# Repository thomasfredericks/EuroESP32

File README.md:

# EuroESP32
 Eurorack version of the ESP32 made to develop modules.

## Features
* 2x audio in 24bits
* 2x audio out 24bits
* 4x CV in (-5V to 5V) 12bits
* 4x CV out (0V to 5V) 12bits

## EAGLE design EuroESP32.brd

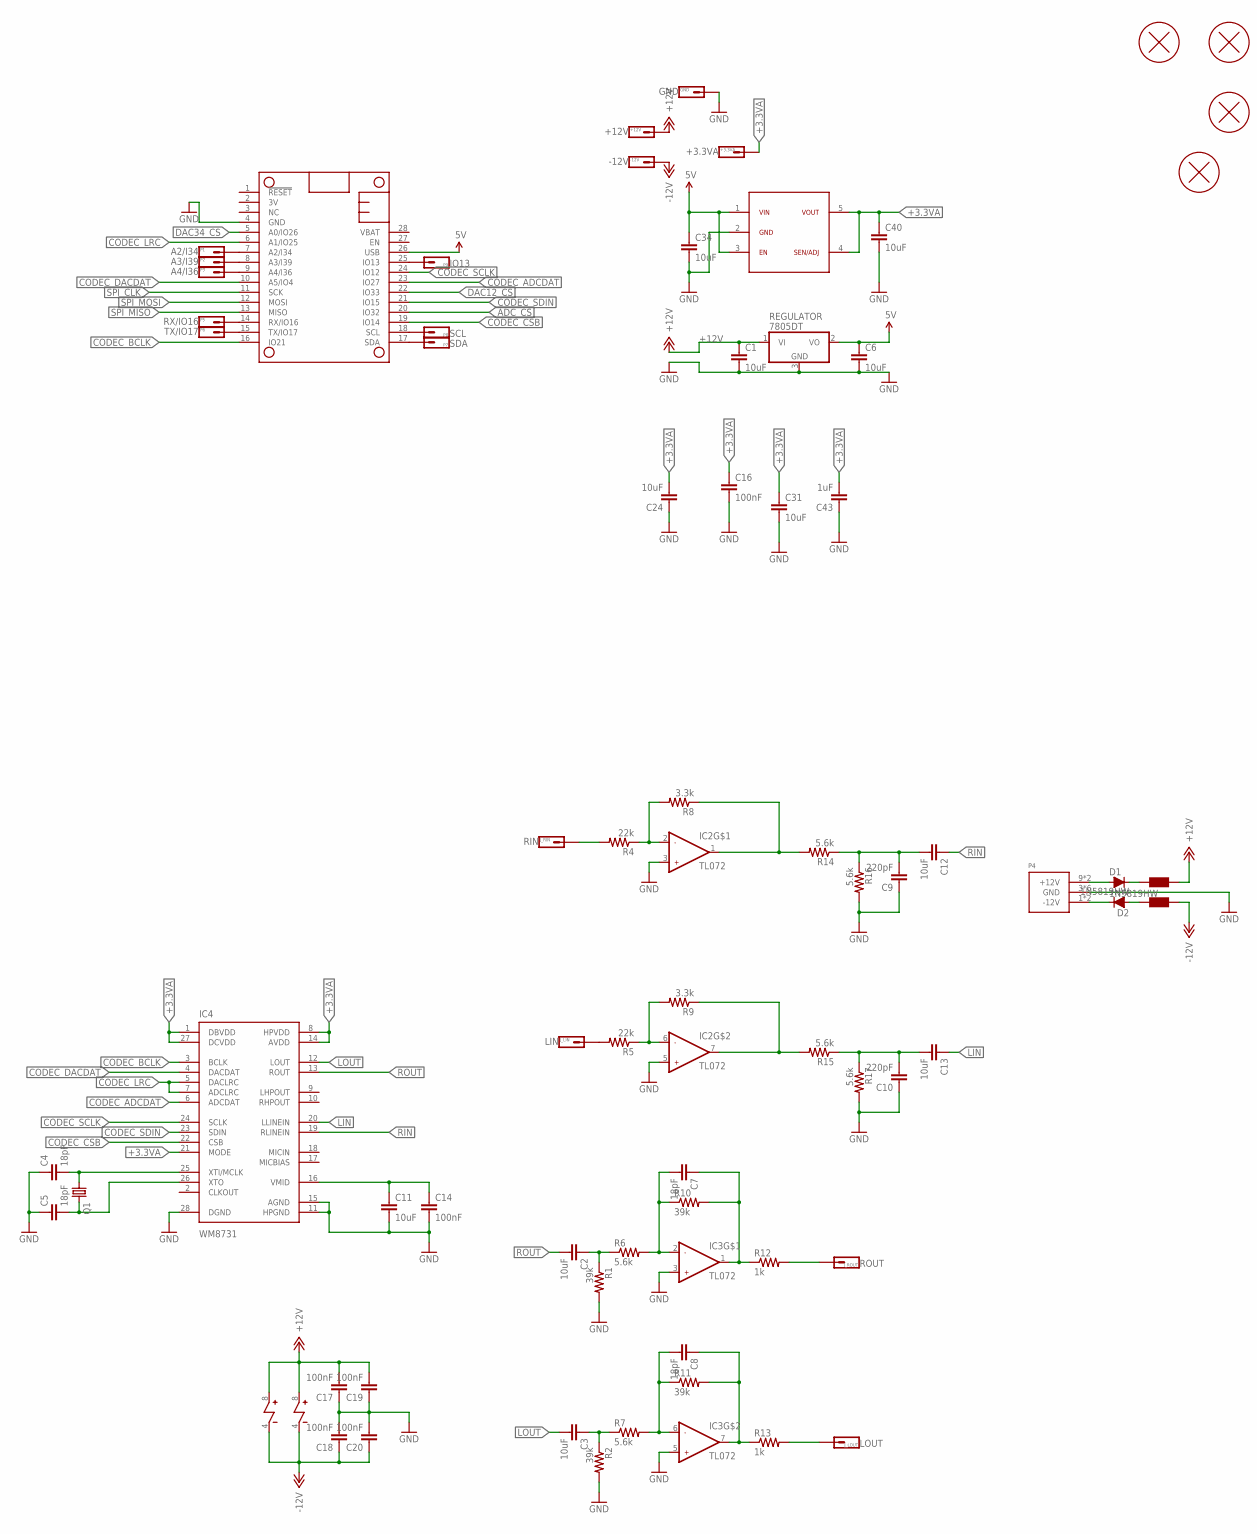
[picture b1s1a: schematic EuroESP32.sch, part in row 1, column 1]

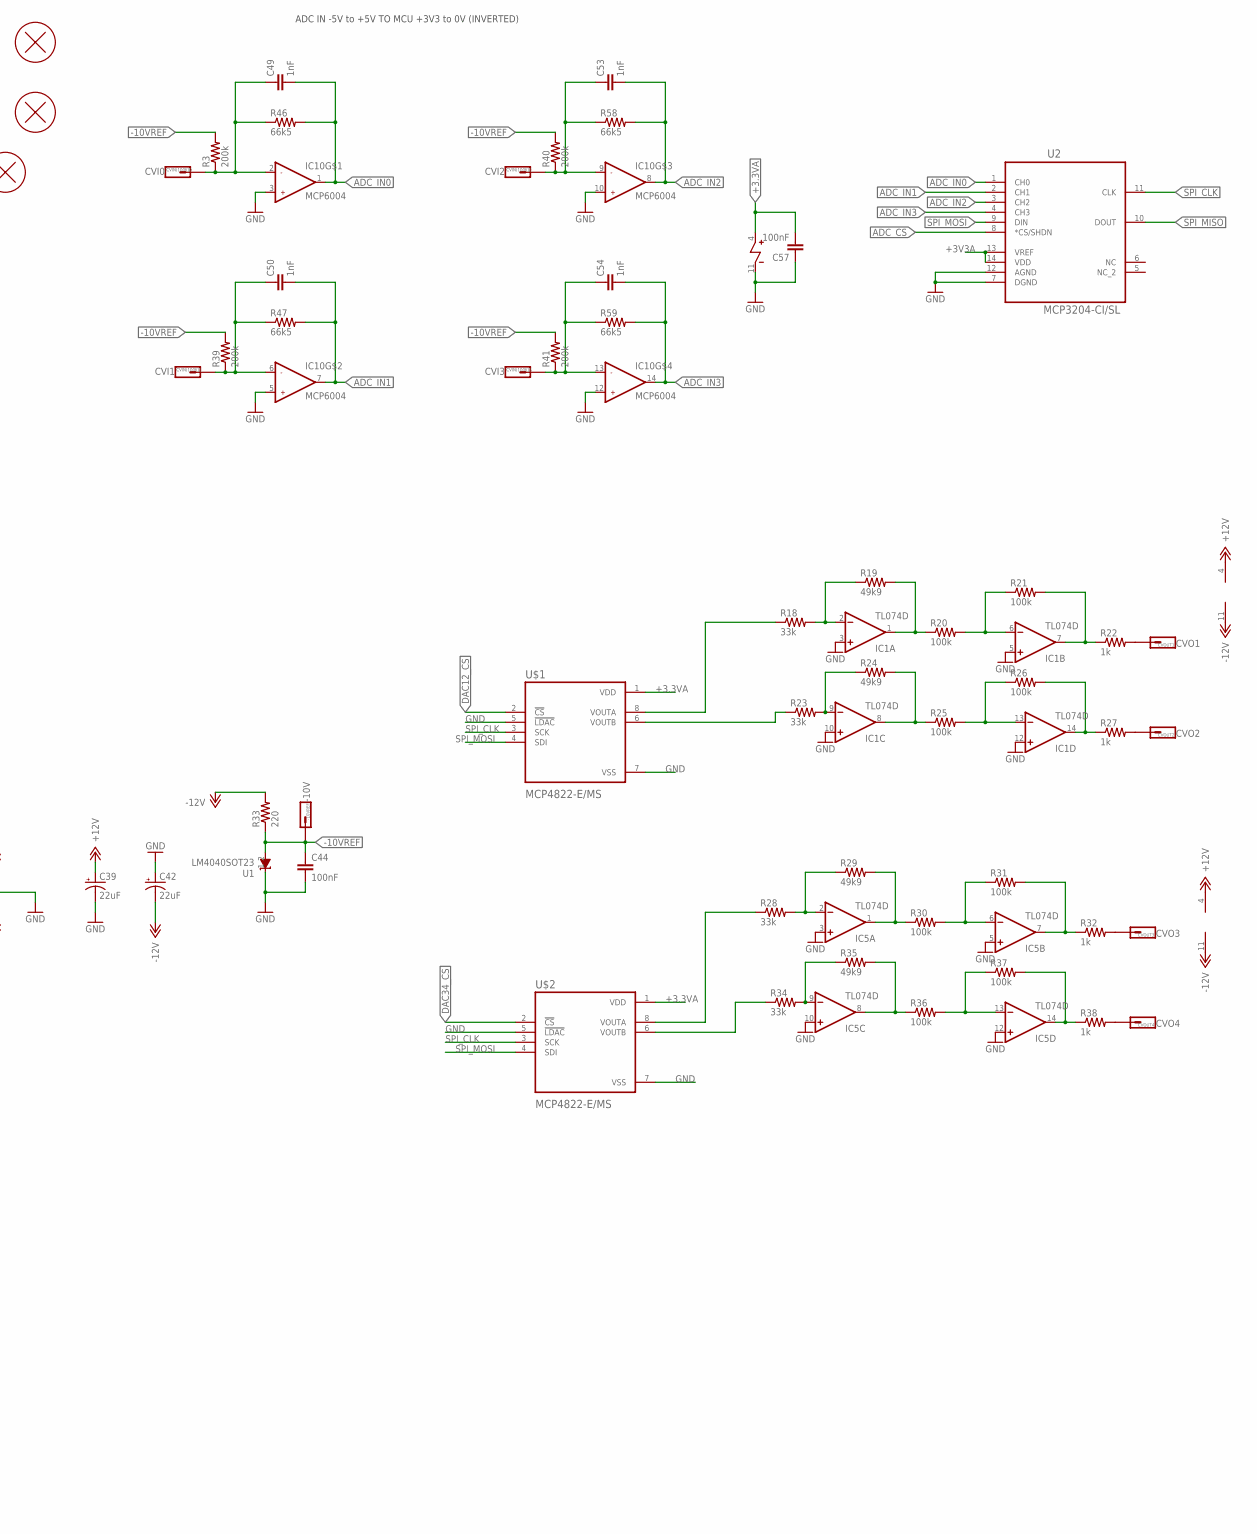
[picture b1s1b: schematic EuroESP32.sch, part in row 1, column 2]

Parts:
+3.3VA: +3.3VA; 1X01_SIDE_NAME
+12V: +12V; 1X01_SIDE_NAME
-10VREF: -10V; 1X01_SIDE_NAME
-12V: -12V; 1X01_SIDE_NAME
C1, C6, C34: 10uF; R1210
C2, C3, C11, C12, C13, C24, C31, C40: 10uF; R0805
C4, C5, C7, C8: 18pF; RESISTOR_0603
C9, C10: 220pF; RESISTOR_0603
C14, C16, C17, C18, C19, C20, C44, C57: 100nF; RESISTOR_0603
C39, C42: 22uF; 1206_POL
C43: 1uF; RESISTOR_0603
C49, C50, C53, C54: 1nF; RESISTOR_0603
CVIN(100K)0: CVI0; 1X01_SIDE_NAME
CVIN(100K)1: CVI1; 1X01_SIDE_NAME
CVIN(100K)2: CVI2; 1X01_SIDE_NAME
CVIN(100K)3: CVI3; 1X01_SIDE_NAME
CVOUT1: CVO1; 1X01_SIDE_NAME
CVOUT2: CVO2; 1X01_SIDE_NAME
CVOUT3: CVO3; 1X01_SIDE_NAME
CVOUT4: CVO4; 1X01_SIDE_NAME
D1, D2: 1N5819HW; SOD123
F1, F2: Würth Electronics 742792664; R0805
GND: GND; 1X01_SIDE_NAME
H1, H3, H4, H5: PCB_SCREW
IC1, IC5: TL074D; SO14
IC2, IC3: TL072; SOIC8
IC4: WM8731; SSOP28
IC7: ADP7118; SOT23-5L
IC10: MCP6004; TSSOP14
J_LIN: LIN; 1X01_SIDE_NAME
J_LOUT: LOUT; 1X01_SIDE_NAME
J_RIN: RIN; 1X01_SIDE_NAME
J_ROUT: ROUT; 1X01_SIDE_NAME
MS2: FEATHER_HUZZAH32NO_DRILL; FEATHERWING_NODRILL
P1: A2/I34; 1X01_SIDE_NAME
P2: A3/I39; 1X01_SIDE_NAME
P3: A4/I36; 1X01_SIDE_NAME
P4: POWER_SIMPLE10; POWER_10
P5: RX/IO16; 1X01_SIDE_NAME
P6: TX/IO17; 1X01_SIDE_NAME
P7: SDA; 1X01_SIDE_NAME
P8: SCL; 1X01_SIDE_NAME
P9: IO13; 1X01_SIDE_NAME
Q1: CRYSTAL; HC49UP
R1, R2, R10, R11: 39k; RESISTOR_0603
R3, R39, R40, R41: 200k; RESISTOR_0603
R4, R5: 22k; RESISTOR_0603
R6, R7, R14, R15, R16, R17: 5.6k; RESISTOR_0603
R8, R9: 3.3k; RESISTOR_0603
R12, R13, R22, R27, R32, R38: 1k; RESISTOR_0603
R18, R23, R28, R34: 33k; RESISTOR_0603
R19, R24, R29, R35: 49k9; RESISTOR_0603
R20, R21, R25, R26, R30, R31, R36, R37: 100k; RESISTOR_0603
R33: 220; RESISTOR_0603
R46, R47, R58, R59: 66k5; RESISTOR_0603
REGULATOR: 7805DT; TO252
U1: LM4040SOT23; SOT23
U2: MCP3204-CI/SL; SOIC127P600X175-14N
U$1, U$2: MCP4822-E/MS; SOP65P490X110-8N

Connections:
5V: C6.1, C34.1, IC7.1, IC7.3, MS2.26 (USB), REGULATOR.2 (VO)
+3.3VA: +3.3VA.1, C16.1, C24.2, C31.1, C40.1, C43.2, C57.2, IC4.1 (DBVDD), IC4.8 (HPVDD), IC4.14 (AVDD), IC4.21 (MODE), IC4.27 (DCVDD), IC7.4, IC7.5, IC10.4, U$1.1 (VDD), U$2.1 (VDD)
+3V3A: U2.13 (VREF), U2.14 (VDD)
+12V: +12V.1, C1.1, C17.2, C19.2, C39.2 (+), F1.1, IC1.4 (V+), IC2.8, IC3.8, IC5.4 (V+), REGULATOR.1 (VI)
-10VREF: -10VREF.1, C44.1, R3.2, R33.1, R39.2, R40.2, R41.2, U1.2 (A)
-12V: -12V.1, C18.1, C20.1, C42.1 (-), F2.1, IC1.11 (V-), IC2.4, IC3.4, IC5.11 (V-), R33.2
ADC_CS: MS2.20 (IO32), U2.8 (*CS/SHDN)
ADC_IN0: C49.2, IC10.1, R46.2, U2.1 (CH0)
ADC_IN1: C50.2, IC10.7, R47.2, U2.2 (CH1)
ADC_IN2: C53.2, IC10.8, R58.2, U2.3 (CH2)
ADC_IN3: C54.2, IC10.14, R59.2, U2.4 (CH3)
CODEC_ADCDAT: IC4.6 (ADCDAT), MS2.23 (IO27)
CODEC_BCLK: IC4.3 (BCLK), MS2.16 (IO21)
CODEC_CSB: IC4.22 (CSB), MS2.19 (IO14)
CODEC_DACDAT: IC4.4 (DACDAT), MS2.10 (A5/IO4)
CODEC_LRC: IC4.5 (DACLRC), IC4.7 (ADCLRC), MS2.6 (A1/IO25)
CODEC_SCLK: IC4.24 (SCLK), MS2.24 (IO12)
CODEC_SDIN: IC4.23 (SDIN), MS2.21 (IO15)
DAC12_CS: MS2.22 (IO33), U$1.2 (!CS)
DAC34_CS: MS2.5 (A0/IO26), U$2.2 (!CS)
DAC_B: R23.1, U$1.6 (VOUTB)
DAC_D: R34.1, U$2.6 (VOUTB)
GND: C1.2, C4.1, C5.1, C6.2, C9.1, C10.1, C11.2, C14.2, C16.2, C17.1, C18.2, C19.1, C20.2, C24.1, C31.2, C34.2, C39.1 (-), C40.2, C42.2 (+), C43.1, C44.2, C57.1, GND.1, IC1.3 (+IN), IC1.5 (+IN), IC1.10 (+IN), IC1.12 (+IN), IC2.3, IC2.5, IC3.3, IC3.5, IC4.11 (HPGND), IC4.15 (AGND), IC4.28 (DGND), IC5.3 (+IN), IC5.5 (+IN), IC5.10 (+IN), IC5.12 (+IN), IC7.2, IC10.3, IC10.5, IC10.10, IC10.11, IC10.12, MS2.4 (GND), P4.3 (GND), P4.4 (GND), P4.5 (GND), P4.6 (GND), P4.7 (GND), P4.8 (GND), R1.2, R2.2, R16.2, R17.2, REGULATOR.3 (GND), U1.1 (C), U2.7 (DGND), U2.12 (AGND), U$1.5 (!LDAC), U$1.7 (VSS), U$2.5 (!LDAC), U$2.7 (VSS)
LIN: C13.1, IC4.20 (LLINEIN)
LOUT: C3.2, IC4.12 (LOUT)
unnamed: J_LIN.1, R5.2
unnamed: J_LOUT.1, R13.2
unnamed: J_ROUT.1, R12.2
unnamed: IC1.2 (-IN), R18.2, R19.1
unnamed: IC1.7 (OUT), R21.2, R22.1
unnamed: IC1.9 (-IN), R23.2, R24.1
unnamed: MS2.7 (A2/I34), P1.1
unnamed: IC1.1 (OUT), R19.2, R20.1
unnamed: IC1.14 (OUT), R26.2, R27.1
unnamed: IC5.6 (-IN), R30.2, R31.1
unnamed: IC1.8 (OUT), R24.2, R25.1
unnamed: IC5.2 (-IN), R28.2, R29.1
unnamed: IC5.7 (OUT), R31.2, R32.1
unnamed: IC5.13 (-IN), R36.2, R37.1
unnamed: C53.1, CVIN(100K)2.1, IC10.9, R40.1, R58.1
unnamed: IC5.1 (OUT), R29.2, R30.1
unnamed: C49.1, CVIN(100K)0.1, IC10.2, R3.1, R46.1
unnamed: IC5.9 (-IN), R34.2, R35.1
unnamed: C50.1, CVIN(100K)1.1, IC10.6, R39.1, R47.1
unnamed: IC5.14 (OUT), R37.2, R38.1
unnamed: C54.1, CVIN(100K)3.1, IC10.13, R41.1, R59.1
unnamed: IC1.6 (-IN), R20.2, R21.1
unnamed: IC5.8 (OUT), R35.2, R36.1
unnamed: R18.1, U$1.8 (VOUTA)
unnamed: CVOUT1.1, R22.2
unnamed: R28.1, U$2.8 (VOUTA)
unnamed: CVOUT2.1, R27.2
unnamed: IC1.13 (-IN), R25.2, R26.1
unnamed: CVOUT3.1, R32.2
unnamed: MS2.8 (A3/I39), P2.1
unnamed: J_RIN.1, R4.2
unnamed: IC2.2, R4.1, R8.2
unnamed: D1.+, P4.9 (+12V), P4.10 (+12V)
unnamed: CVOUT4.1, R38.2
unnamed: MS2.9 (A4/I36), P3.1
unnamed: IC2.1, R8.1, R14.2
unnamed: C9.2, C12.2, R14.1, R16.1
unnamed: MS2.14 (RX/IO16), P5.1
unnamed: MS2.15 (TX/IO17), P6.1
unnamed: IC2.6, R5.1, R9.2
unnamed: MS2.17 (SDA), P7.1
unnamed: IC2.7, R9.1, R15.2
unnamed: C5.2, IC4.26 (XTO), Q1.2
unnamed: C4.2, IC4.25 (XTI/MCLK), Q1.1
unnamed: C10.2, C13.2, R15.1, R17.1
unnamed: C7.1, IC3.1, R10.2, R12.1
unnamed: D1.-, F1.2
unnamed: C7.2, IC3.2, R6.2, R10.1
unnamed: C2.1, R1.1, R6.1
unnamed: MS2.18 (SCL), P8.1
unnamed: MS2.25 (IO13), P9.1
unnamed: D2.-, P4.1 (-12V), P4.2 (-12V)
unnamed: C8.1, IC3.7, R11.2, R13.1
unnamed: C8.2, IC3.6, R7.2, R11.1
unnamed: C11.1, C14.1, IC4.16 (VMID)
unnamed: C3.1, R2.1, R7.1
unnamed: D2.+, F2.2
RIN: C12.1, IC4.19 (RLINEIN)
ROUT: C2.2, IC4.13 (ROUT)
SPI_CLK: MS2.11 (SCK), U2.11 (CLK), U$1.3 (SCK), U$2.3 (SCK)
SPI_MISO: MS2.13 (MISO), U2.10 (DOUT)
SPI_MOSI: MS2.12 (MOSI), U2.9 (DIN), U$1.4 (SDI), U$2.4 (SDI)

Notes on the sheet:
ADC IN -5V to +5V TO MCU +3V3 to 0V (INVERTED)

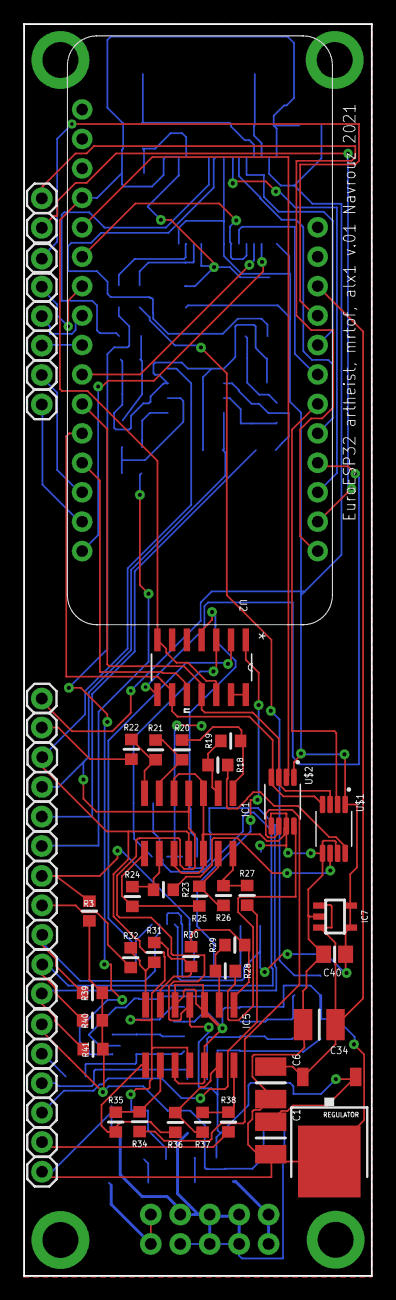
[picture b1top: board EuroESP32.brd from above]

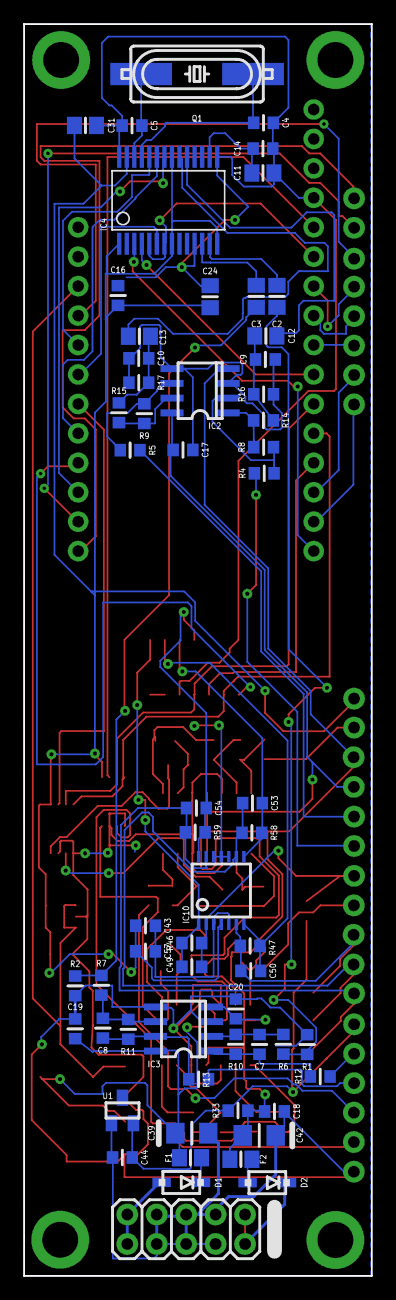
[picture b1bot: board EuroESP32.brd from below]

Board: 2 copper layers, 30.0 x 108.0 mm, 125 parts (60 on the bottom side), 87 nets.

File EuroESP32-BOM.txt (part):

Partlist exported from C:/Users/tofredericks/OneDrive/Création/Eurorack Circuits/EuroESP32/EuroESP32.sch at 2021-03-19 12:49

Qty Value                    Device                   Package             Parts                                                      Description                AVAILABILITY DESCRIPTION                                   MF                   MP           MPN           OC_FARNELL OC_NEWARK PACKAGE          POPULARITY PRICE PURCHASE-URL                                                  SUPPLIER 
1                            CRYSTAL                  HC49UP              Q1                                                                                                                                                                                                                                                                                                                             
2                            DIODE                    SOD123              D1, D2                                                                                                                                                                                                                                                                                                                         
1   +12V                     HEADER-1X1               1X01_SIDE_NAME      +12V                                                       Header 1                                                                                                                                                                                                                                                            
1   +3.3VA                   HEADER-1X1               1X01_SIDE_NAME      +3.3VA                                                     Header 1                                                                                                                                                                                                                                                            
1   -10VREF                  HEADER-1X1               1X01_SIDE_NAME      -10VREF                                                    Header 1                                                                                                                                                                                                                                                            
1   -12V                     HEADER-1X1               1X01_SIDE_NAME      -12V                                                       Header 1                                                                                                                                                                                                                                                            
8   100k                     RESISTOR                 RESISTOR_0603       R20, R21, R25, R26, R30, R31, R36, R37                                                                                                                                                                                                                                                                                         
12  100nF                    CAPACITOR                RESISTOR_0603       C14, C16, C17, C18, C19, C20, C27, C29, C30, C44, C46, C57                                                                                                                                                                                                                                                                     
2   10uF                     C2.5/2                   C2.5-2              C1, C6                                                     CAPACITOR                                                                                                                                                                                                                                                           
12  10uF                     CAPACITOR0805            R0805               C2, C3, C11, C12, C13, C15, C23, C24, C25, C31, C32, C40                                                                                                                                                                                                                                                                       
1   10uF                     CAPACITOR1210            R1210               C34                                                                                                                                                                                                                                                                                                                            
4   18pF                     CAPACITOR                RESISTOR_0603       C4, C5, C7, C8                                                                                                                                                                                                                                                                                                                 
6   1k                       RESISTOR                 RESISTOR_0603       R12, R13, R22, R27, R32, R38                                                                                                                                                                                                                                                                                                   
4   1nF                      CAPACITOR                RESISTOR_0603       C49, C50, C53, C54                                                                                                                                                                                                                                                                                                             
2   1uF                      CAPACITOR                RESISTOR_0603       C43, C45                                                                                                                                                                                                                                                                                                                       
4   200k                     RESISTOR                 RESISTOR_0603       R3, R39, R40, R41                                                                                                                                                                                                                                                                                                              
1   220                      RESISTOR                 RESISTOR_0603       R33                                                                                                                                                                                                                                                                                                                            
2   220pF                    CAPACITOR                RESISTOR_0603       C9, C10                                                                                                                                                                                                                                                                                                                        
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
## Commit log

2021-03-19 A few corrections
2021-03-21 Added groups in schematic
2021-03-21 Changed voltage regulator
2021-03-22 Added groups and merged changes from alx-1
2021-03-22 Moved connecters to the side
2021-03-22 Update EuroESP32.brd
    v0.2
    Proper spacing for the main connector
2021-03-22 Create EuroESP32_2021-03-22.zip
    For board houses
2021-03-23 Added extra connectors
2021-03-23 Added a little information
2021-03-23 Just names and a date
2021-03-23 Up to date CAM data
2021-04-21 Lower board (not the top panel)
2021-04-22 Updated BOM

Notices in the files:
parts and their libraries:
SparkFun-Aesthetics: Licensing: Creative Commons ShareAlike 4.0 International - https://creativecommons.org/licenses/by-sa/4.0
